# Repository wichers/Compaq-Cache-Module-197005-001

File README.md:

# Compaq 197005-001 Cache Module reproduction

Reverse Engineered non standard 256KB/1MB L2 Cache Module for use in:

- [Compaq ProLinea 4/66 (164560-001)](https://theretroweb.com/motherboards/s/compaq-prolinea-4-66)
- [Compaq Presario 833CDS/850/850CDS/860CDS/866 (197023-001)](https://theretroweb.com/motherboards/s/compaq-presario-800)
- [Compaq Presario 700-900 series](https://theretroweb.com/motherboards/s/compaq-presario-700-900-series-486)

# Resources
Original 128KB module [front ](/197005-001_front.jpg?raw=true), [back ](/197005-001_back.jpg?raw=true)

[plugged into Prolinea 4/100](/197005-001_front_2.jpg?raw=true)

-----
This project was possible with help provided by rasz_pl - creator of the - [FIC-486-GAC-2 Cache Module reproduction](https://github.com/raszpl/FIC-486-GAC-2-Cache-Module). Huge thank you for inspiration and taking time to review.

[VL82C481 datasheet](/vl82c481-633364566fabe183309250.pdf)

[VESA VLB slot pinout](/VLB_pins.png) [VESA VLB slot dimensions](/vlb-edge-conn.png)

# Progress report

16/8/2025: Added switch to set memory size

31/8/2024: Added support for switchable 256KB/1MB

28/8/2024: First version up for testing.

23/8/2024: Project start. Figuring out the pinout and matching to datasheet.

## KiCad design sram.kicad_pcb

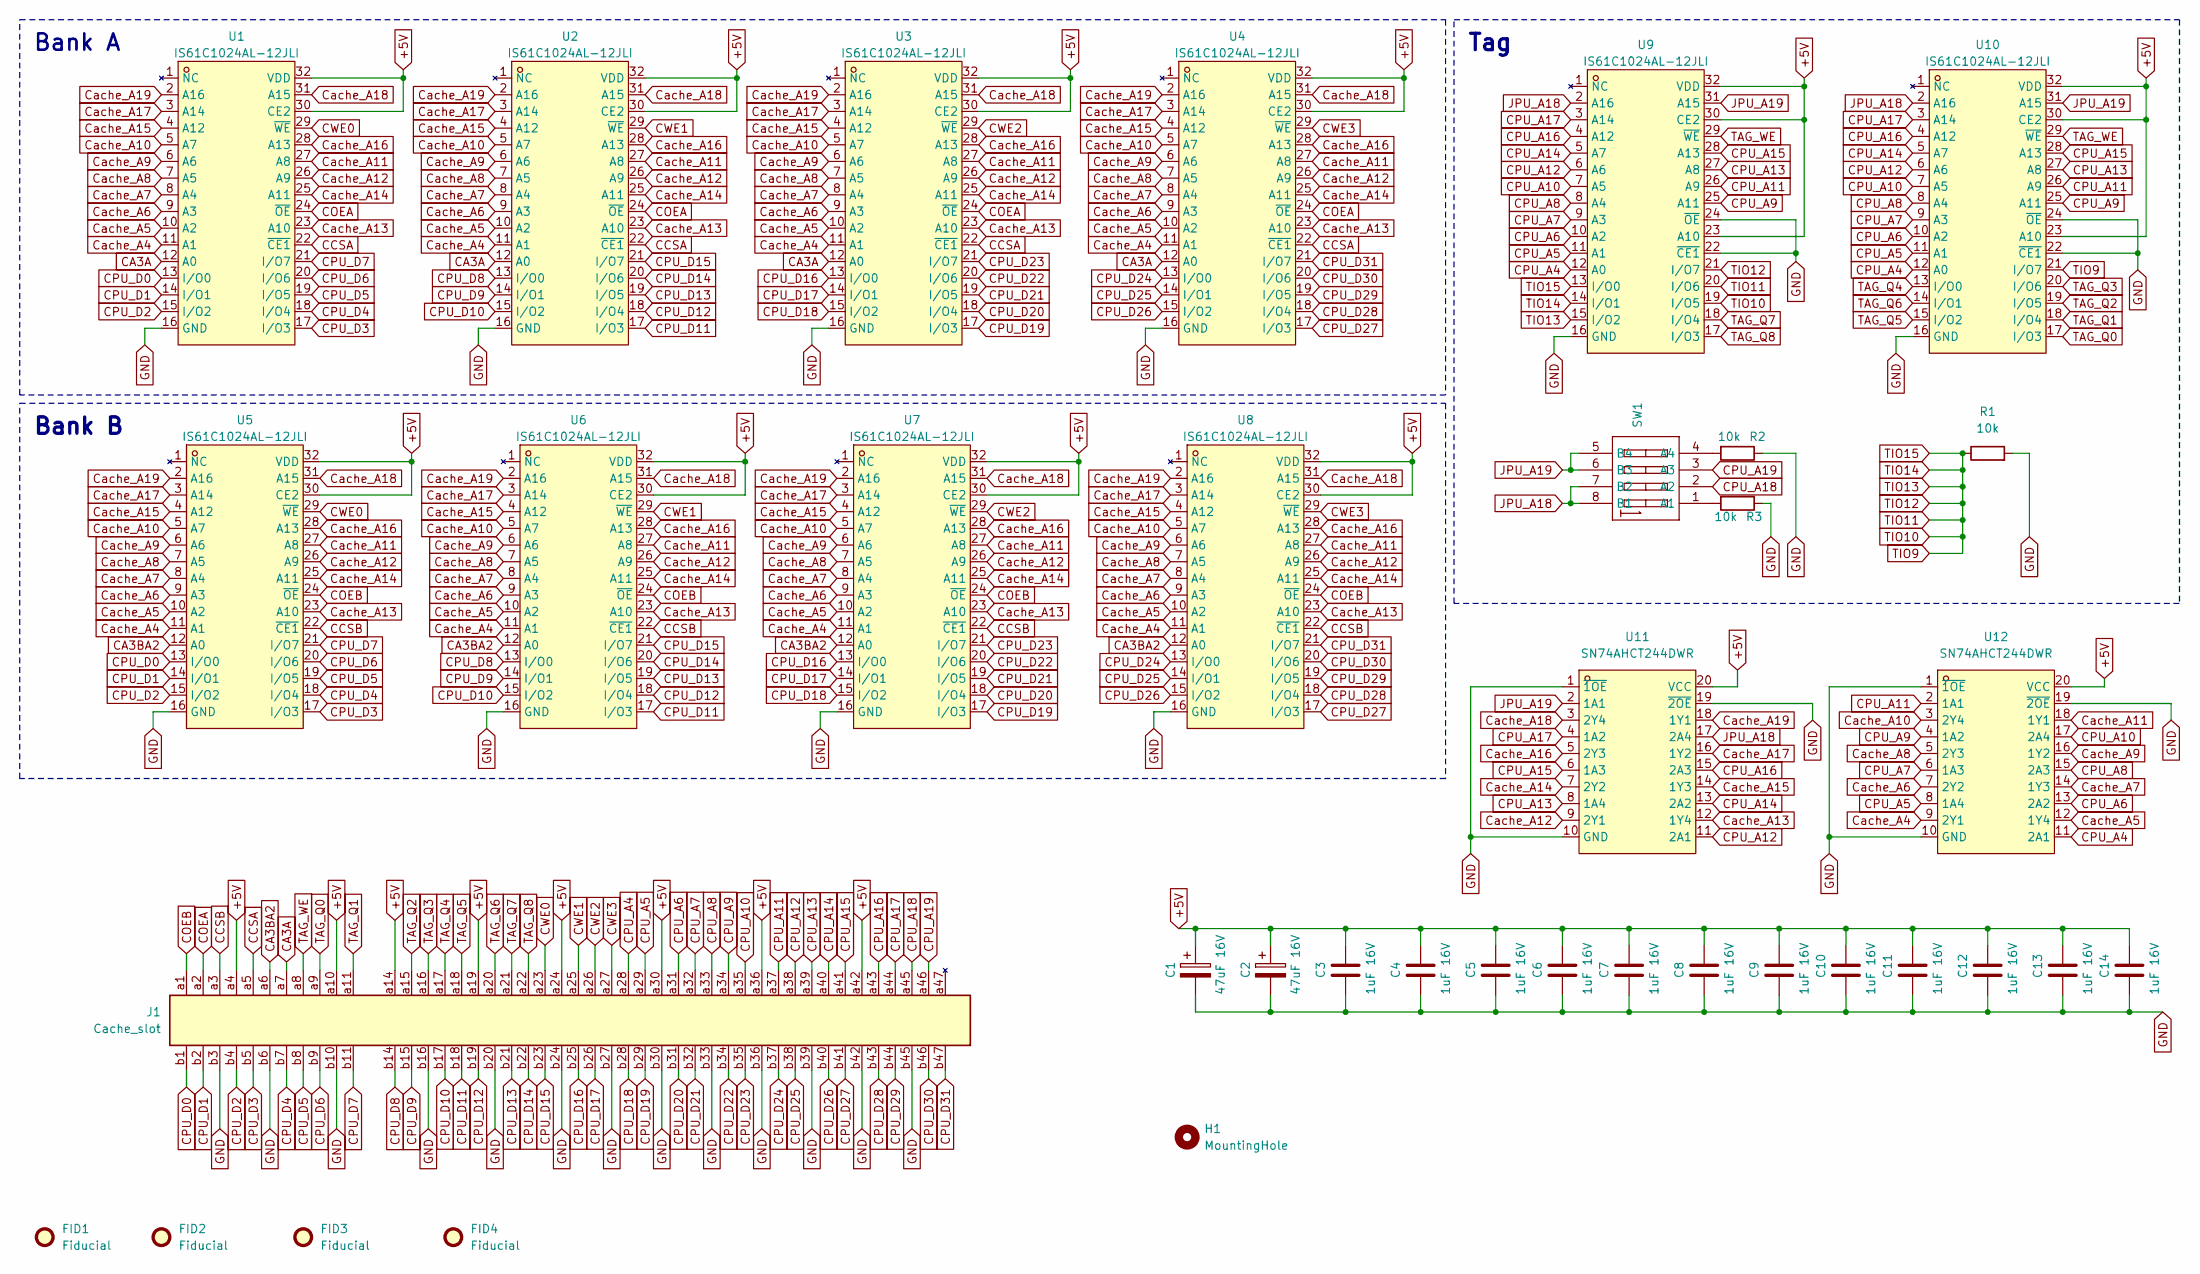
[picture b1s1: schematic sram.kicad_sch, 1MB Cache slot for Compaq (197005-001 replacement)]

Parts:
C1, C2: 47uF 16V; C_1206_3216Metric_Pad1.33x1.80mm_HandSolder
C3, C4, C5, C6, C7, C8, C9, C10, C11, C12, C13, C14: 1uF 16V; C_0805_2012Metric
FID1, FID2, FID3, FID4: Fiducial; Fiducial_0.5mm_Mask1mm
H1: MountingHole; MountingHole_4mm
J1: Cache_slot; Cache slot
R1, R2, R3: 10k; R_0603_1608Metric
SW1: DSIC04TSGET; SW-SMD_8P-L11.1-W6.2-P2.54-LS9.8; LCSC Part C126850
U1, U2, U3, U4, U5, U6, U7, U8, U9, U10: IS61C1024AL-12JLI; SOJ-32_L21.0-W7.6-P1.27-LS8.5-BL; LCSC Part C412832
U11, U12: SN74AHCT244DWR; SOIC-20_L12.8-W7.5-P1.27-LS10.3-BL; LCSC Part C2675568

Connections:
+5V: C1.1, C2.1, C3.1, C4.1, C5.1, C6.1, C7.1, C8.1, C9.1, C10.1, C11.1, C12.1, C13.1, C14.1, J1.a4, J1.a10, J1.a14, J1.a19, J1.a24, J1.a30, J1.a36, J1.a42, U1.30 (CE2), U1.32 (VDD), U2.30 (CE2), U2.32 (VDD), U3.30 (CE2), U3.32 (VDD), U4.30 (CE2), U4.32 (VDD), U5.30 (CE2), U5.32 (VDD), U6.30 (CE2), U6.32 (VDD), U7.30 (CE2), U7.32 (VDD), U8.30 (CE2), U8.32 (VDD), U9.23 (A10), U9.30 (CE2), U9.32 (VDD), U10.23 (A10), U10.30 (CE2), U10.32 (VDD), U11.20 (VCC), U12.20 (VCC)
CA3A: J1.a7, U1.12 (A0), U2.12 (A0), U3.12 (A0), U4.12 (A0)
CA3BA2: J1.a6, U5.12 (A0), U6.12 (A0), U7.12 (A0), U8.12 (A0)
CCSA: J1.a5, U1.22 (~CE1), U2.22 (~CE1), U3.22 (~CE1), U4.22 (~CE1)
CCSB: J1.a3, U5.22 (~CE1), U6.22 (~CE1), U7.22 (~CE1), U8.22 (~CE1)
COEA: J1.a2, U1.24 (~OE), U2.24 (~OE), U3.24 (~OE), U4.24 (~OE)
COEB: J1.a1, U5.24 (~OE), U6.24 (~OE), U7.24 (~OE), U8.24 (~OE)
CPU_A4: J1.a28, U9.12 (A0), U10.12 (A0), U12.11 (2A1)
CPU_A5: J1.a29, U9.11 (A1), U10.11 (A1), U12.8 (1A4)
CPU_A6: J1.a31, U9.10 (A2), U10.10 (A2), U12.13 (2A2)
CPU_A7: J1.a32, U9.9 (A3), U10.9 (A3), U12.6 (1A3)
CPU_A8: J1.a33, U9.8 (A4), U10.8 (A4), U12.15 (2A3)
CPU_A9: J1.a34, U9.25 (A11), U10.25 (A11), U12.4 (1A2)
CPU_A10: J1.a35, U9.7 (A5), U10.7 (A5), U12.17 (2A4)
CPU_A11: J1.a37, U9.26 (A9), U10.26 (A9), U12.2 (1A1)
CPU_A12: J1.a38, U9.6 (A6), U10.6 (A6), U11.11 (2A1)
CPU_A13: J1.a39, U9.27 (A8), U10.27 (A8), U11.8 (1A4)
CPU_A14: J1.a40, U9.5 (A7), U10.5 (A7), U11.13 (2A2)
CPU_A15: J1.a41, U9.28 (A13), U10.28 (A13), U11.6 (1A3)
CPU_A16: J1.a43, U9.4 (A12), U10.4 (A12), U11.15 (2A3)
CPU_A17: J1.a44, U9.3 (A14), U10.3 (A14), U11.4 (1A2)
CPU_A18: J1.a45, SW1.2 (A2)
CPU_A19: J1.a46, SW1.3 (A3)
CPU_D0: J1.b1, U1.13 (I/O0), U5.13 (I/O0)
CPU_D1: J1.b2, U1.14 (I/O1), U5.14 (I/O1)
CPU_D2: J1.b4, U1.15 (I/O2), U5.15 (I/O2)
CPU_D3: J1.b5, U1.17 (I/O3), U5.17 (I/O3)
CPU_D4: J1.b7, U1.18 (I/O4), U5.18 (I/O4)
CPU_D5: J1.b8, U1.19 (I/O5), U5.19 (I/O5)
CPU_D6: J1.b9, U1.20 (I/O6), U5.20 (I/O6)
CPU_D7: J1.b11, U1.21 (I/O7), U5.21 (I/O7)
CPU_D8: J1.b14, U2.13 (I/O0), U6.13 (I/O0)
CPU_D9: J1.b15, U2.14 (I/O1), U6.14 (I/O1)
CPU_D10: J1.b17, U2.15 (I/O2), U6.15 (I/O2)
CPU_D11: J1.b18, U2.17 (I/O3), U6.17 (I/O3)
CPU_D12: J1.b19, U2.18 (I/O4), U6.18 (I/O4)
CPU_D13: J1.b21, U2.19 (I/O5), U6.19 (I/O5)
CPU_D14: J1.b22, U2.20 (I/O6), U6.20 (I/O6)
CPU_D15: J1.b23, U2.21 (I/O7), U6.21 (I/O7)
CPU_D16: J1.b25, U3.13 (I/O0), U7.13 (I/O0)
CPU_D17: J1.b26, U3.14 (I/O1), U7.14 (I/O1)
CPU_D18: J1.b28, U3.15 (I/O2), U7.15 (I/O2)
CPU_D19: J1.b29, U3.17 (I/O3), U7.17 (I/O3)
CPU_D20: J1.b31, U3.18 (I/O4), U7.18 (I/O4)
CPU_D21: J1.b32, U3.19 (I/O5), U7.19 (I/O5)
CPU_D22: J1.b34, U3.20 (I/O6), U7.20 (I/O6)
CPU_D23: J1.b35, U3.21 (I/O7), U7.21 (I/O7)
CPU_D24: J1.b37, U4.13 (I/O0), U8.13 (I/O0)
CPU_D25: J1.b38, U4.14 (I/O1), U8.14 (I/O1)
CPU_D26: J1.b40, U4.15 (I/O2), U8.15 (I/O2)
CPU_D27: J1.b41, U4.17 (I/O3), U8.17 (I/O3)
CPU_D28: J1.b43, U4.18 (I/O4), U8.18 (I/O4)
CPU_D29: J1.b44, U4.19 (I/O5), U8.19 (I/O5)
CPU_D30: J1.b46, U4.20 (I/O6), U8.20 (I/O6)
CPU_D31: J1.b47, U4.21 (I/O7), U8.21 (I/O7)
CWE0: J1.a23, U1.29 (~WE), U5.29 (~WE)
CWE1: J1.a25, U2.29 (~WE), U6.29 (~WE)
CWE2: J1.a26, U3.29 (~WE), U7.29 (~WE)
CWE3: J1.a27, U4.29 (~WE), U8.29 (~WE)
Cache_A4: U1.11 (A1), U2.11 (A1), U3.11 (A1), U4.11 (A1), U5.11 (A1), U6.11 (A1), U7.11 (A1), U8.11 (A1), U12.9 (2Y1)
Cache_A5: U1.10 (A2), U2.10 (A2), U3.10 (A2), U4.10 (A2), U5.10 (A2), U6.10 (A2), U7.10 (A2), U8.10 (A2), U12.12 (1Y4)
Cache_A6: U1.9 (A3), U2.9 (A3), U3.9 (A3), U4.9 (A3), U5.9 (A3), U6.9 (A3), U7.9 (A3), U8.9 (A3), U12.7 (2Y2)
Cache_A7: U1.8 (A4), U2.8 (A4), U3.8 (A4), U4.8 (A4), U5.8 (A4), U6.8 (A4), U7.8 (A4), U8.8 (A4), U12.14 (1Y3)
Cache_A8: U1.7 (A5), U2.7 (A5), U3.7 (A5), U4.7 (A5), U5.7 (A5), U6.7 (A5), U7.7 (A5), U8.7 (A5), U12.5 (2Y3)
Cache_A9: U1.6 (A6), U2.6 (A6), U3.6 (A6), U4.6 (A6), U5.6 (A6), U6.6 (A6), U7.6 (A6), U8.6 (A6), U12.16 (1Y2)
Cache_A10: U1.5 (A7), U2.5 (A7), U3.5 (A7), U4.5 (A7), U5.5 (A7), U6.5 (A7), U7.5 (A7), U8.5 (A7), U12.3 (2Y4)
Cache_A11: U1.27 (A8), U2.27 (A8), U3.27 (A8), U4.27 (A8), U5.27 (A8), U6.27 (A8), U7.27 (A8), U8.27 (A8), U12.18 (1Y1)
Cache_A12: U1.26 (A9), U2.26 (A9), U3.26 (A9), U4.26 (A9), U5.26 (A9), U6.26 (A9), U7.26 (A9), U8.26 (A9), U11.9 (2Y1)
Cache_A13: U1.23 (A10), U2.23 (A10), U3.23 (A10), U4.23 (A10), U5.23 (A10), U6.23 (A10), U7.23 (A10), U8.23 (A10), U11.12 (1Y4)
Cache_A14: U1.25 (A11), U2.25 (A11), U3.25 (A11), U4.25 (A11), U5.25 (A11), U6.25 (A11), U7.25 (A11), U8.25 (A11), U11.7 (2Y2)
Cache_A15: U1.4 (A12), U2.4 (A12), U3.4 (A12), U4.4 (A12), U5.4 (A12), U6.4 (A12), U7.4 (A12), U8.4 (A12), U11.14 (1Y3)
Cache_A16: U1.28 (A13), U2.28 (A13), U3.28 (A13), U4.28 (A13), U5.28 (A13), U6.28 (A13), U7.28 (A13), U8.28 (A13), U11.5 (2Y3)
Cache_A17: U1.3 (A14), U2.3 (A14), U3.3 (A14), U4.3 (A14), U5.3 (A14), U6.3 (A14), U7.3 (A14), U8.3 (A14), U11.16 (1Y2)
Cache_A18: U1.31 (A15), U2.31 (A15), U3.31 (A15), U4.31 (A15), U5.31 (A15), U6.31 (A15), U7.31 (A15), U8.31 (A15), U11.3 (2Y4)
Cache_A19: U1.2 (A16), U2.2 (A16), U3.2 (A16), U4.2 (A16), U5.2 (A16), U6.2 (A16), U7.2 (A16), U8.2 (A16), U11.18 (1Y1)
GND: C1.2, C2.2, C3.2, C4.2, C5.2, C6.2, C7.2, C8.2, C9.2, C10.2, C11.2, C12.2, C13.2, C14.2, J1.b3, J1.b6, J1.b10, J1.b16, J1.b20, J1.b24, J1.b27, J1.b30, J1.b33, J1.b36, J1.b39, J1.b42, J1.b45, R1.2, R2.1, R3.1, U1.16 (GND), U2.16 (GND), U3.16 (GND), U4.16 (GND), U5.16 (GND), U6.16 (GND), U7.16 (GND), U8.16 (GND), U9.16 (GND), U9.22 (~CE1), U9.24 (~OE), U10.16 (GND), U10.22 (~CE1), U10.24 (~OE), U11.1 (~1OE), U11.10 (GND), U11.19 (~2OE), U12.1 (~1OE), U12.10 (GND), U12.19 (~2OE)
JPU_A18: SW1.7 (B2), SW1.8 (B1), U9.2 (A16), U10.2 (A16), U11.17 (2A4)
JPU_A19: SW1.5 (B4), SW1.6 (B3), U9.31 (A15), U10.31 (A15), U11.2 (1A1)
unnamed: R3.2, SW1.1 (A1)
unnamed: R2.2, SW1.4 (A4)
TAG_Q0: J1.a9, U10.17 (I/O3)
TAG_Q1: J1.a11, U10.18 (I/O4)
TAG_Q2: J1.a15, U10.19 (I/O5)
TAG_Q3: J1.a16, U10.20 (I/O6)
TAG_Q4: J1.a17, U10.13 (I/O0)
TAG_Q5: J1.a18, U10.15 (I/O2)
TAG_Q6: J1.a20, U10.14 (I/O1)
TAG_Q7: J1.a21, U9.18 (I/O4)
TAG_Q8: J1.a22, U9.17 (I/O3)
TAG_WE: J1.a8, U9.29 (~WE), U10.29 (~WE)
TIO10: R1.1, U9.13 (I/O0), U9.14 (I/O1), U9.15 (I/O2), U9.19 (I/O5), U9.20 (I/O6), U9.21 (I/O7), U10.21 (I/O7)

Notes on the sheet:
Bank A
Tag
Bank B

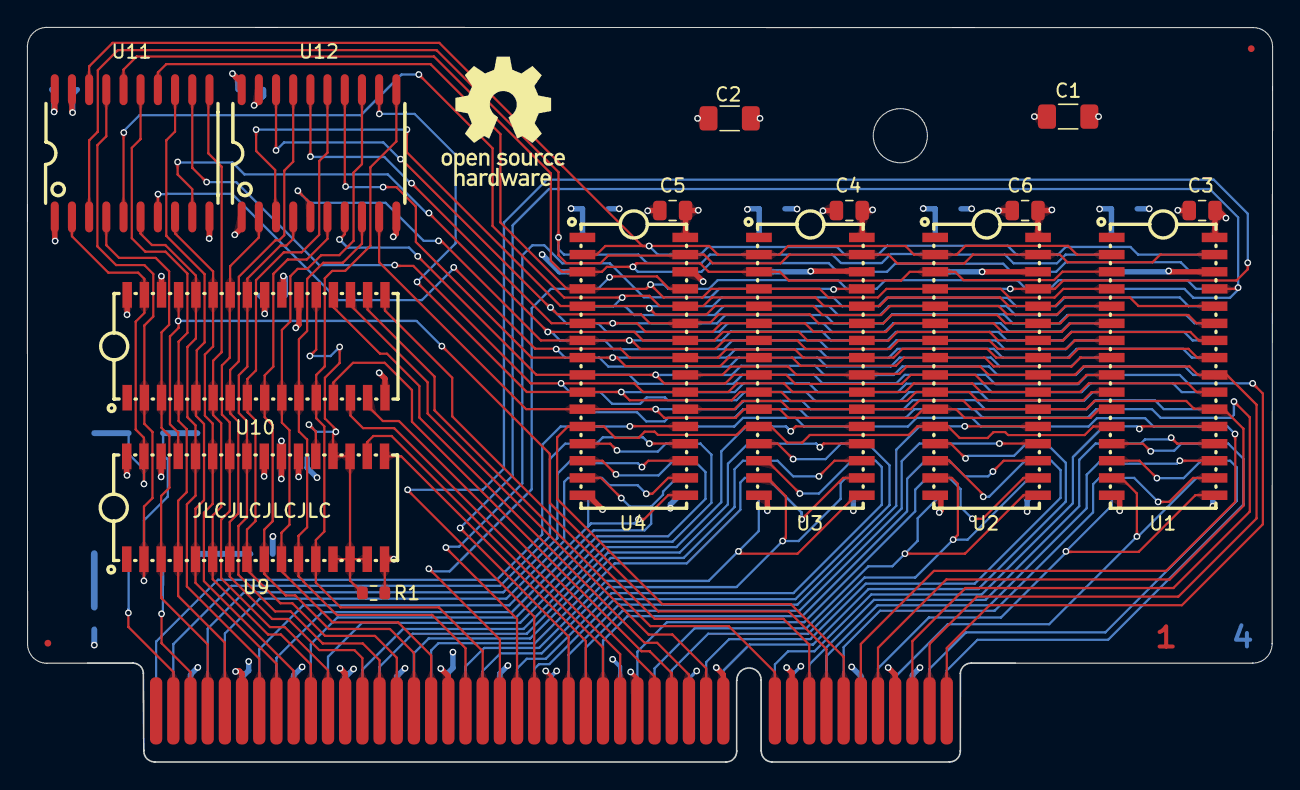
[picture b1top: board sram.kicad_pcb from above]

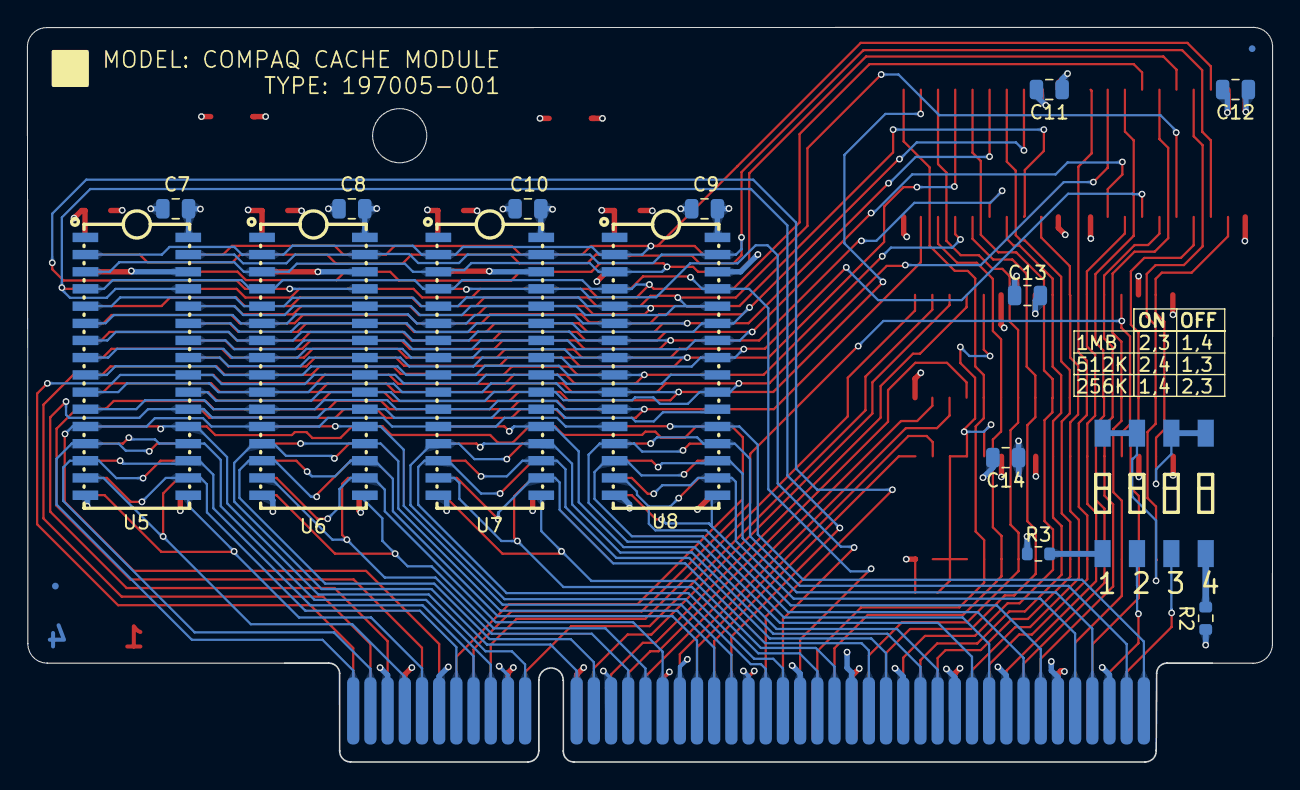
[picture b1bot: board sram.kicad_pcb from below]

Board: 4 copper layers, 91.9 x 54.2 mm, 36 parts (17 on the bottom side), 91 nets.

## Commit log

2024-08-28 inital commit
2024-08-29 change from rasz_pl: - moving VIAs apart - change resistor network with single resistor
2024-08-30 pass DRC with rounded tracks
2024-08-31 updated to 256KB/1MB
2024-08-31 Added support for switchable 256KB/1MB
2024-09-02 cleanup
2025-08-16 added switch to set memory size
